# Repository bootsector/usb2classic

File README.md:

# USB2Classic - USB controllers adapter for retro consoles!
(c) Bruno Freitas - 04/2019 - http://www.brunofreitas.com/  

This project is Open Source (GPLv3) and Open Hardware (CC BY-SA 4.0)  

I've bought some super-cheap STM8S 8-bit microcontroller based boards and I 
was wondering what kind of cool project I could put them to use. I've mixed
it with an USB Host Mini 2.0 module a CPLD and some discrete components and
then the USB2Classic adapter was born!

This adapter allows you to use USB controllers with old consoles, such as:

* Sega Genesis / Mega Drive (can emulate either a 3 button or 6 button pad)
* Sega Master System, Atari 2600 and others
* Panasonic 3DO
* NES
* Super NES
* Sega Saturn
* Neo Geo
* TG16/PC-Engine (through adapter board connected to the Neo Geo output)

Currently compatible USB controllers are:

* Playstation 4 USB controller
* XBOX 360 USB controller (and compatible XInput devices)
* XBOX 360 USB Wireless Receiver
* 8BitDo Wireless USB Adapter (in XInput mode)
* Some PS3/PS4/XBOX360 USB arcade stick controllers

The CPLD originally used by this adapter is an EPM7064SLC44-10N which is 5V
based. Verilog sources are inside the multi-out directory along with Quartus II
project files.

The USB Host Mini board **MUST** be modified for 5V as shown in the
doc/usbhost_mini_5v_mod.png diagram.

Firmware was compiled using SDCC version 3.8.0

Thanks to Bruno Duarte Gouveia (brNX) for all the help with Verilog!

Enjoy!

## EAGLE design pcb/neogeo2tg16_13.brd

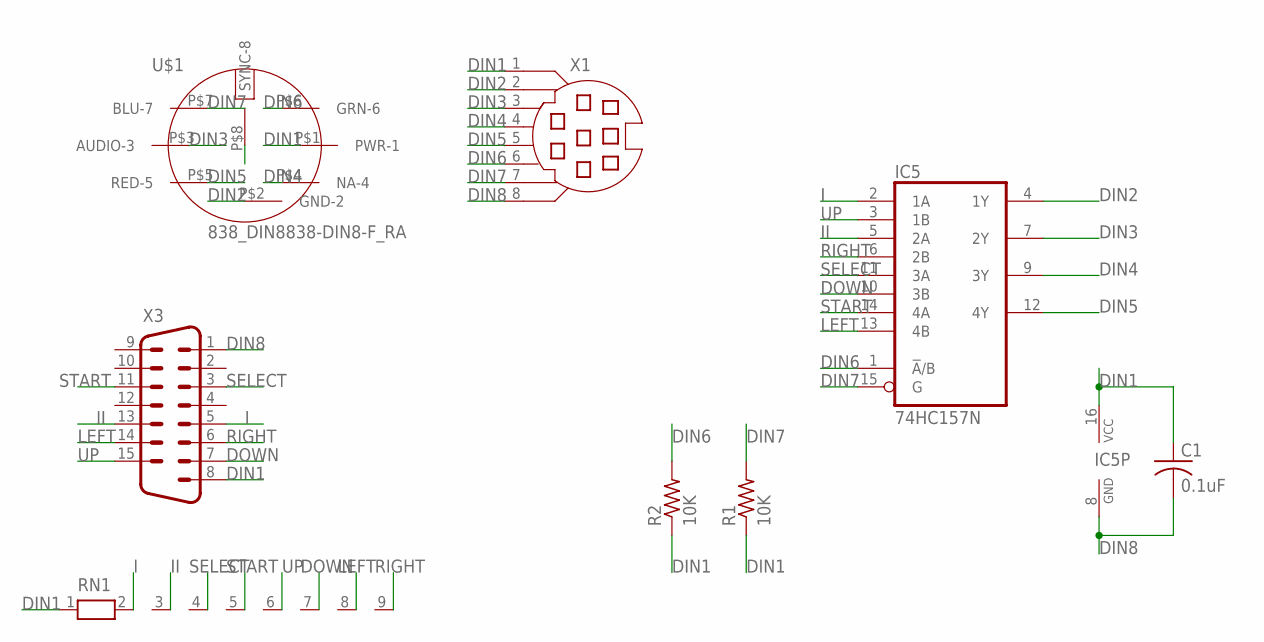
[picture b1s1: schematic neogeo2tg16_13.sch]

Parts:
C1: 0.1uF; C025-024X044
IC5: 74HC157N; DIL16
R1, R2: 10K; 0204/7
RN1: RN08; RN-9
U$1: 838_DIN8838-DIN8-F_RA; 838_DIN8
X1: MD08SS; MDIN08SS
X3: M15HP

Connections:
DIN1: C1.1, IC5.16 (VCC), R1.1, R2.1, RN1.1, U$1.P$1 (PWR-1), X1.1, X3.8
DIN2: IC5.4 (1Y), U$1.P$2 (GND-2), X1.2
DIN3: IC5.7 (2Y), U$1.P$3 (AUDIO-3), X1.3
DIN4: IC5.9 (3Y), U$1.P$4 (NA-4), X1.4
DIN5: IC5.12 (4Y), U$1.P$5 (RED-5), X1.5
DIN6: IC5.1 (!A!/B), R2.2, U$1.P$6 (GRN-6), X1.6
DIN7: IC5.15 (G), R1.2, U$1.P$7 (BLU-7), X1.7
DIN8: C1.2, IC5.8 (GND), U$1.P$8 (SYNC-8), X1.8, X3.1
DOWN: IC5.10 (3B), RN1.7, X3.7
I: IC5.2 (1A), RN1.2, X3.5
II: IC5.5 (2A), RN1.3, X3.13
LEFT: IC5.13 (4B), RN1.8, X3.14
RIGHT: IC5.6 (2B), RN1.9, X3.6
SELECT: IC5.11 (3A), RN1.4, X3.3
START: IC5.14 (4A), RN1.5, X3.11
UP: IC5.3 (1B), RN1.6, X3.15

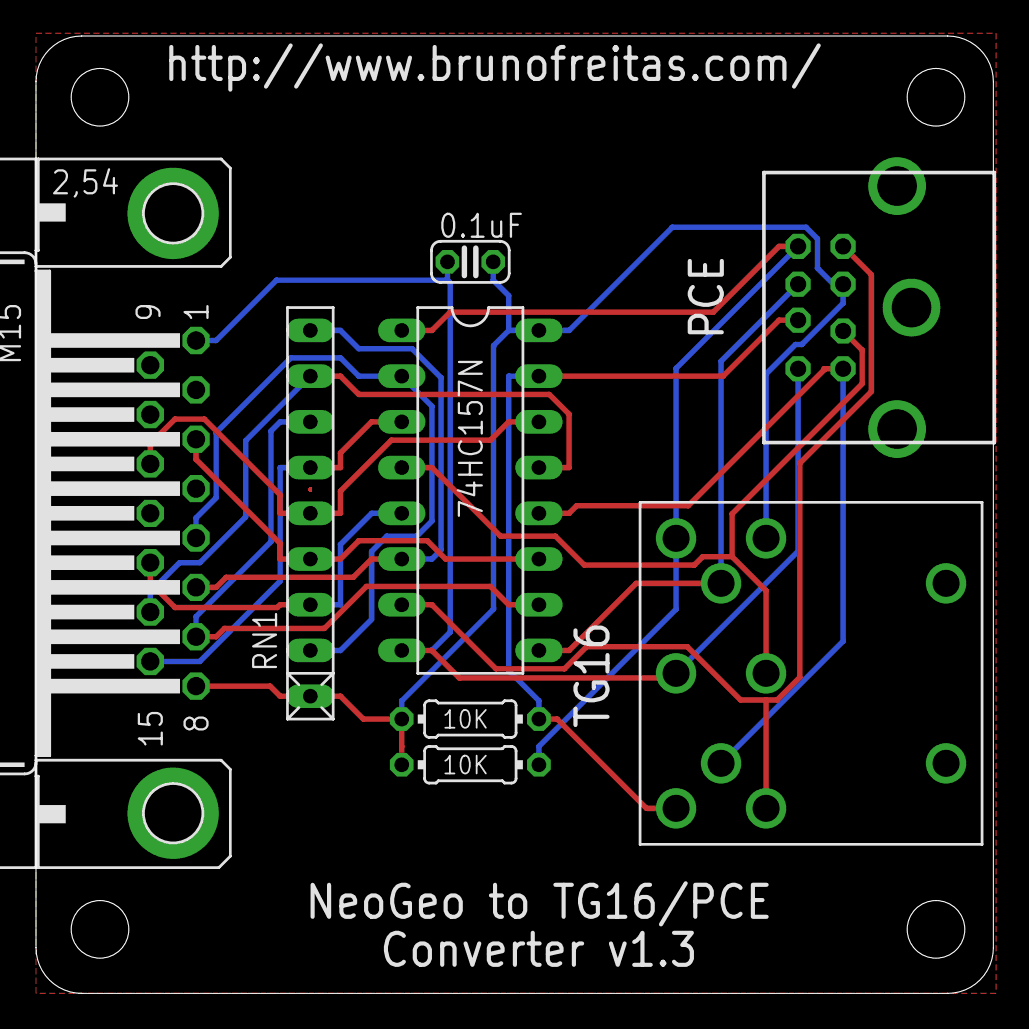
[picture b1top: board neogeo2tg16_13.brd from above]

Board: 2 copper layers, 53.2 x 53.2 mm, 8 parts (0 on the bottom side), 16 nets.

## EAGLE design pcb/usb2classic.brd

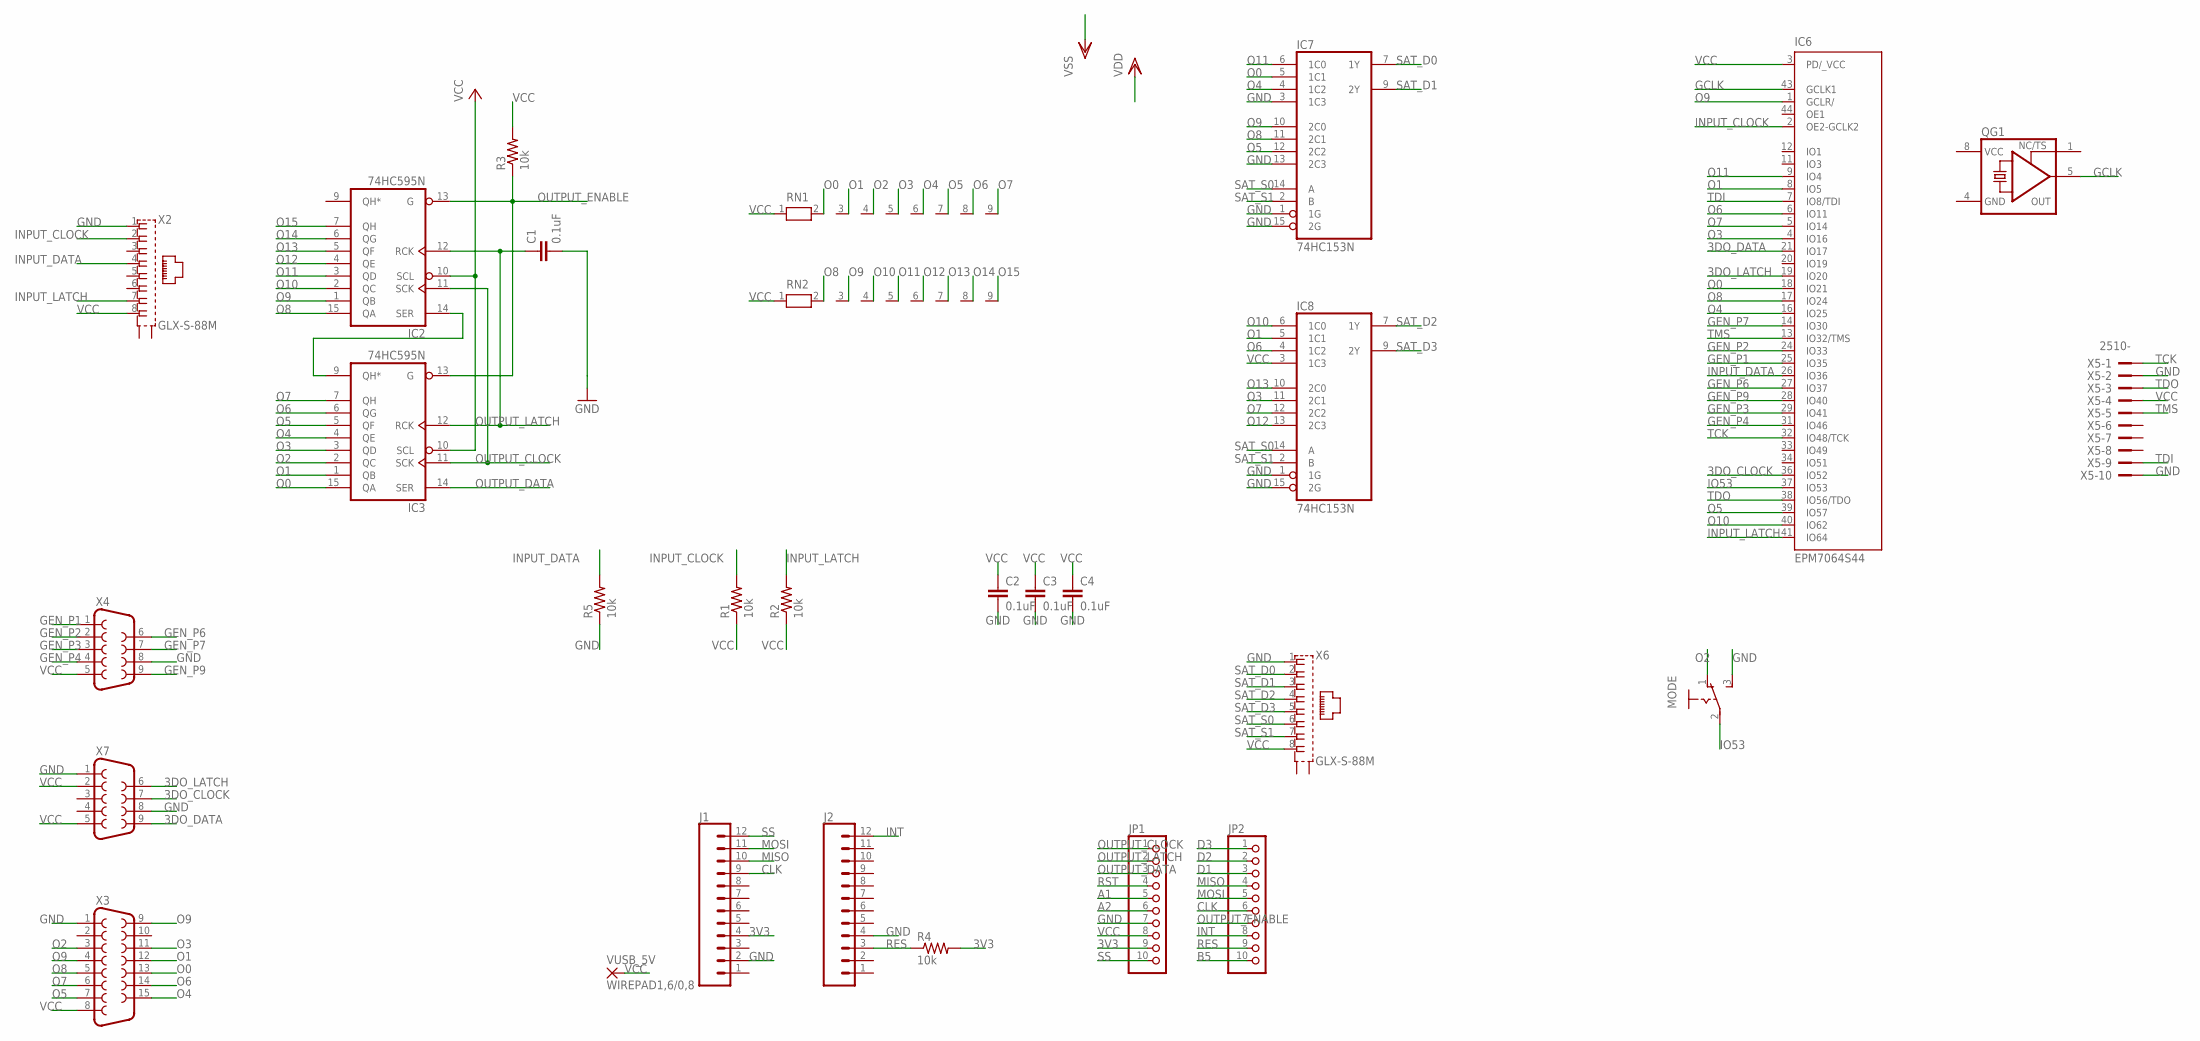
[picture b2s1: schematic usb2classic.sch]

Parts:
C1, C2, C3, C4: 0.1uF; C050-024X044
IC2, IC3: 74HC595N; DIL16
IC6: EPM7064S44; PLCC-S44
IC7, IC8: 74HC153N; DIL16
J1, J2: CONN_12; 1X12
JP1, JP2: PINHD-1X10; 1X10
MODE: CHAVE
QG1: XO-8; DIL08S
R1, R2, R3, R4, R5: 10k; 0207/10
RN1, RN2: RN08; RN-9
VUSB_5V: WIREPAD1,6/0,8; 1,6/0,8
X2, X6: GLX-S-88M
X3: F15HP
X4, X7: F09HP
X5: 2510-; PAK100/2500-10

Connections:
3DO_CLOCK: IC6.36 (IO52), X7.7
3DO_DATA: IC6.21 (IO17), X7.9
3DO_LATCH: IC6.19 (IO20), X7.6
3V3: J1.4, JP1.9, R4.2
A1: JP1.5
A2: JP1.6
B5: JP2.10
CLK: J1.9, JP2.6
D1: JP2.3
D2: JP2.2
D3: JP2.1
GCLK: IC6.43 (GCLK1), QG1.5 (OUT)
GEN_P1: IC6.25 (IO35), X4.1
GEN_P2: IC6.24 (IO33), X4.2
GEN_P3: IC6.29 (IO41), X4.3
GEN_P4: IC6.31 (IO46), X4.4
GEN_P6: IC6.27 (IO37), X4.6
GEN_P7: IC6.14 (IO30), X4.7
GEN_P9: IC6.28 (IO40), X4.9
GND: C1.2, C2.2, C3.2, C4.2, IC2.8 (GND), IC3.8 (GND), IC6.10 (GND), IC6.22 (GND), IC6.30 (GND), IC6.42 (GND), IC7.1 (1G), IC7.3 (1C3), IC7.8 (GND), IC7.13 (2C3), IC7.15 (2G), IC8.1 (1G), IC8.8 (GND), IC8.15 (2G), J1.2, J2.4, JP1.7, MODE.3 (S), QG1.4 (GND), R5.1, X2.1, X3.1, X4.8, X5.2, X5.10, X6.1, X7.1, X7.8
INPUT_CLOCK: IC6.2 (OE2-GCLK2), R1.2, X2.2
INPUT_DATA: IC6.26 (IO36), R5.2, X2.4
INPUT_LATCH: IC6.41 (IO64), R2.2, X2.7
INT: J2.12, JP2.8
IO53: IC6.37 (IO53), MODE.2
MISO: J1.10, JP2.4
MOSI: J1.11, JP2.5
unnamed: IC2.14 (SER), IC3.9 (QH*)
O0: IC3.15 (QA), IC6.18 (IO21), IC7.5 (1C1), RN1.2, X3.13
O1: IC3.1 (QB), IC6.8 (IO5), IC8.5 (1C1), RN1.3, X3.12
O2: IC3.2 (QC), MODE.1 (O), RN1.4, X3.3
O3: IC3.3 (QD), IC6.4 (IO16), IC8.11 (2C1), RN1.5, X3.11
O4: IC3.4 (QE), IC6.16 (IO25), IC7.4 (1C2), RN1.6, X3.15
O5: IC3.5 (QF), IC6.39 (IO57), IC7.12 (2C2), RN1.7, X3.7
O6: IC3.6 (QG), IC6.6 (IO11), IC8.4 (1C2), RN1.8, X3.14
O7: IC3.7 (QH), IC6.5 (IO14), IC8.12 (2C2), RN1.9, X3.6
O8: IC2.15 (QA), IC6.17 (IO24), IC7.11 (2C1), RN2.2, X3.5
O9: IC2.1 (QB), IC6.1 (GCLR/), IC7.10 (2C0), RN2.3, X3.4, X3.9
O10: IC2.2 (QC), IC6.40 (IO62), IC8.6 (1C0), RN2.4
O11: IC2.3 (QD), IC6.9 (IO4), IC7.6 (1C0), RN2.5
O12: IC2.4 (QE), IC8.13 (2C3), RN2.6
O13: IC2.5 (QF), IC8.10 (2C0), RN2.7
O14: IC2.6 (QG), RN2.8
O15: IC2.7 (QH), RN2.9
OUTPUT_CLOCK: IC2.11 (SCK), IC3.11 (SCK), JP1.1
OUTPUT_DATA: IC3.14 (SER), JP1.3
OUTPUT_ENABLE: IC2.13 (G), IC3.13 (G), JP2.7, R3.1
OUTPUT_LATCH: C1.1, IC2.12 (RCK), IC3.12 (RCK), JP1.2
RES: J2.3, JP2.9, R4.1
RST: JP1.4
SAT_D0: IC7.7 (1Y), X6.2
SAT_D1: IC7.9 (2Y), X6.3
SAT_D2: IC8.7 (1Y), X6.4
SAT_D3: IC8.9 (2Y), X6.5
SAT_S0: IC7.14 (A), IC8.14 (A), X6.6
SAT_S1: IC7.2 (B), IC8.2 (B), X6.7
SS: J1.12, JP1.10
TCK: IC6.32 (IO48/TCK), X5.1
TDI: IC6.7 (IO8/TDI), X5.9
TDO: IC6.38 (IO56/TDO), X5.3
TMS: IC6.13 (IO32/TMS), X5.5
VCC: C2.1, C3.1, C4.1, IC2.10 (SCL), IC2.16 (VCC), IC3.10 (SCL), IC3.16 (VCC), IC6.3 (PD/_VCC), IC6.15 (VCC), IC6.23 (VCC), IC6.35 (VCC), IC7.16 (VCC), IC8.3 (1C3), IC8.16 (VCC), JP1.8, QG1.8 (VCC), R1.1, R2.1, R3.2, RN1.1, RN2.1, VUSB_5V.1, X2.8, X3.8, X4.5, X5.4, X6.8, X7.2, X7.5

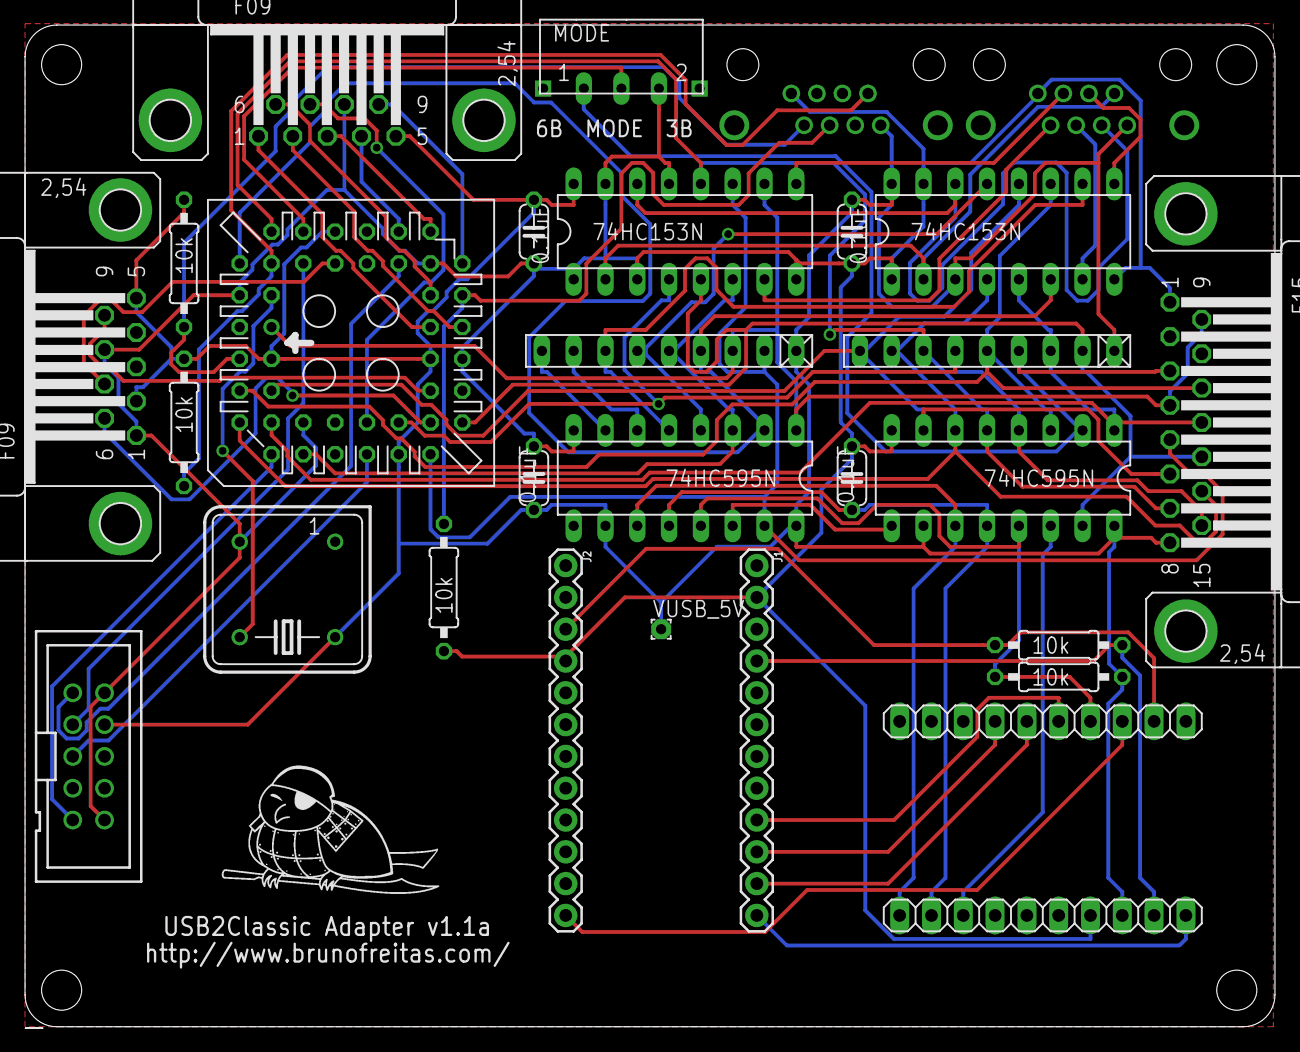
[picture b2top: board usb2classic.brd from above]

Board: 2 copper layers, 99.8 x 80.0 mm, 29 parts (0 on the bottom side), 55 nets.

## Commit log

2019-05-13 Initial release
2019-05-14 Removed warning from Quartus. Restored SMD timeout register to 14 bits
2019-05-14 Added support for Madcatz TE2 (PS3/PS4 modes) arcade stick
2019-05-14 README.md update
2019-05-16 Adding SVG and PDF for acrylic case
2019-05-16 Add support to Toodles MC Cthulhu USB board
2019-05-25 Decreasing brightness of Dualshock 4 as it was drawing too much current
2019-05-25 Added support to Brook Universal Board (Forced PS4 Mode)
2019-05-28 Adding support for Brook Universal Fighting Stick (X360 force mode)
2019-06-22 Added button mapping reference
2019-07-29 Map analog shoulder triggers to L2/R2
2019-07-29 Map analog shoulder triggers to L2/R2 - Improved
2019-08-07 Added pull-down resistor to NES/SNES data line. This is an attempt to fix issue #1
2019-08-13 Added support for the QuadStick (www.quadstick.com)
2019-09-11 Making shift-out comms more stable
2019-09-15 Setting unused pins on the CPLD as input tri-stated
2019-09-25 Fix L2/R2 trigger data for X360 pad and receiver
2019-10-03 Adding support for extra button mappings
2019-10-03 Added one more button map config
2019-10-03 Changes in the default mapping
2019-10-03 Updated button mapping document
2019-10-04 Added one more config map
2019-10-04 Mappings optimizations
2019-10-04 Mapping corrections
2019-10-07 Added some PS3/PS3 arcade controllers to the detection tables
2019-10-19 Removed combos for home button. Map switching is now done with Up + Home. Updated map 4. Updated mapping doc
2019-10-25 Removed not used signal traces from the CPLD
2019-10-29 Support right analog stick as alternative to buttons for Xeno Crisis on Sega Genesis
2020-04-24 Fixed start button not working in the NeoGeo to TG16 adapter
2020-07-31 Fixed 3DO output support in multi-out CPLD module
2020-08-01 Improved stability of SNES/NES output in multi-out CPLD module
2020-08-09 Getting rid of async external signals for NES/SNES and 3DO encoders.

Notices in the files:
parts and their libraries:
SparkFun-Connectors: Licensing: Creative Commons ShareAlike 4.0 International - https://creativecommons.org/licenses/by-sa/4.0
